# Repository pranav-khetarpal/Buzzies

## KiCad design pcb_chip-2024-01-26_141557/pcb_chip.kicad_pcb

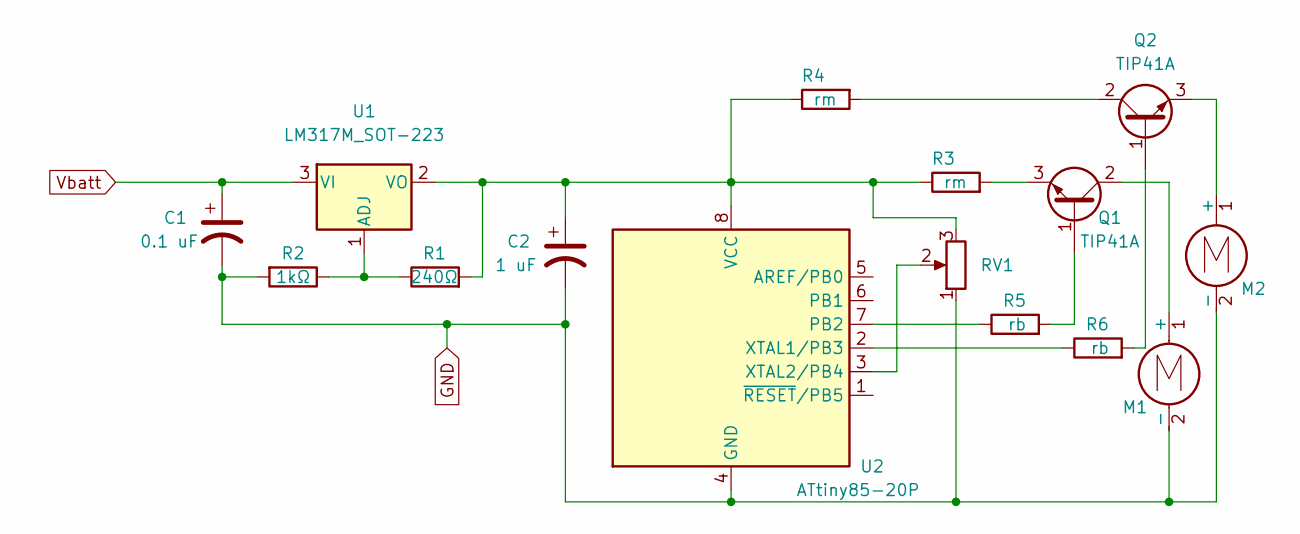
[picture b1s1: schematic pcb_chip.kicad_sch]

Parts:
C1: 0.1 uF; CP_Elec_4x5.4
C2: 1 uF; CP_Elec_4x5.4
M1, M2: vib_mot; PinHeader_1x02_P2.54mm_Vertical
Q1, Q2: TIP41A; SOT-23
R1: 240Ω; R_1206_3216Metric
R2: 1kΩ; R_1206_3216Metric
R3, R4: rm; R_1206_3216Metric
R5, R6: rb; R_1206_3216Metric
RV1: R_Potentiometer
U1: LM317M_SOT-223; SOT-223-3_TabPin2
U2: ATtiny85-20P; DIP-8_W7.62mm

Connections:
GND: C1.2, C2.2, M1.2 (-), M2.2 (-), R2.2, RV1.1, U2.4 (GND); also elsewhere on the board
unnamed: M1.1 (+), Q1.2 (C)
unnamed: M2.1 (+), Q2.3 (E)
unnamed: Q1.1 (B), R5.2
unnamed: Q1.3 (E), R3.2
unnamed: Q2.1 (B), R6.2
unnamed: Q2.2 (C), R4.2
unnamed: R1.1, R2.1, U1.1 (ADJ)
unnamed: C2.1, R1.2, R3.1, R4.1, RV1.3, U1.2 (VO), U2.8 (VCC)
unnamed: R5.1, U2.7 (PB2)
unnamed: R6.1, U2.2 (XTAL1/PB3)
unnamed: RV1.2, U2.3 (XTAL2/PB4)
Vbatt: C1.1, U1.3 (VI); also elsewhere on the board

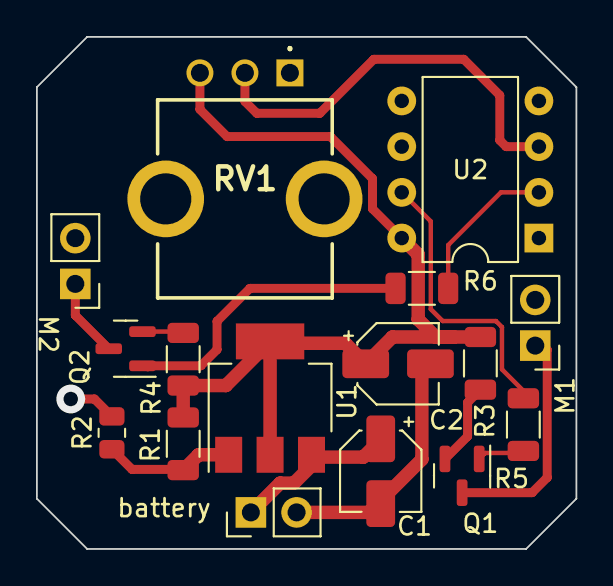
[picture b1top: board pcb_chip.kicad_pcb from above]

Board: 2 copper layers, 30.0 x 28.4 mm, 16 parts (0 on the bottom side), 13 nets.

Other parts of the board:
battery: vib_mot; PinHeader_1x02_P2.54mm_Vertical

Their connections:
GND: battery.2 (-); also elsewhere on the board
Vbatt: battery.1 (+); also elsewhere on the board

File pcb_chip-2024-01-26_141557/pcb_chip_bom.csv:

"Id";"Designator";"Footprint";"Quantity";"Designation";"Supplier and ref";
1;"U2";"DIP-8_W7.62mm";1;"ATtiny85-20P";;;
2;"R6,R5";"R_1206_3216Metric";2;"rb";;;
3;"Q1,Q2";"SOT-23";2;"TIP41A";;;
4;"R3,R4";"R_1206_3216Metric";2;"rm";;;
5;"C2";"CP_Elec_4x5.4";1;"1 uF";;;
6;"R2";"R_0805_2012Metric";1;"1kΩ";;;
7;"R1";"R_1206_3216Metric";1;"240Ω";;;
8;"RV1";"PTV09A4030SA503";1;"R_Potentiometer";;;
9;"M2,M1,battery";"PinHeader_1x02_P2.54mm_Vertical";3;"vib_mot";;;
10;"C1";"CP_Elec_4x5.4";1;"0.1 uF";;;
11;"U1";"SOT-223-3_TabPin2";1;"LM317M_SOT-223";;;

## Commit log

2024-10-14 Initial Upload
2024-10-15 Working intensity and time change
2024-11-03 Update with pcb chip files
2025-01-09 Moving Unneeded Arduino Files
2025-01-09 Cleaning Up Unneeded Projects
